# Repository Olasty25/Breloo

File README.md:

# Breloo — a round video keychain

A Ø40 mm keychain that plays actual video. A 1.28" round GC9A01 LCD on the front,
an ESP32-S3 and a microSD slot on the back, a 3.7 V LiPo and USB-C charging.
Drop MP4-derived frames on the card, clip it to your keys, and it loops video in
your pocket.

I am a high-school student from Poland. This is my first 4-layer board and my
first board with a fine-pitch FPC connector.

## What it does

- Plays video and images from a microSD card on a 240×240 round IPS display
- Charges over USB-C, runs from a 400 mAh LiPo
- Backlight is PWM-dimmable from the MCU
- Battery voltage is measured through a divider so the firmware can show charge level
- Fits a 3D-printed case that clips onto a keyring

## Specs

| | |
|---|---|
| Board | Ø40.0 mm circle, 4 layers, 1.6 mm FR-4 |
| MCU | ESP32-S3-WROOM-1-N16R2 (16 MB flash, 2 MB PSRAM) |
| Display | GC9A01 1.28" round IPS 240×240, 12-pin 0.5 mm FPC |
| Storage | microSD (Hirose DM3AT-SF-PEJM5), 1-bit SPI |
| Power | USB-C 5 V → MCP73831 charger → 3.7 V LiPo → AP2112K-3.3 LDO |
| Battery | LP402025, 3.7 V, ~400 mAh |
| Stack-up | F.Cu signals / In1 solid GND / In2 solid +3V3 / B.Cu signals |
| Design rules | 0.2 mm trace / 0.2 mm clearance, 0.6/0.3 mm vias |
| Components | 35 placed parts, 11 top / 24 bottom |
| DRC | 0 errors, 0 unconnected, schematic/PCB parity clean |

## The interesting problem: the display tape is reversed

The GC9A01 flex tape leaves the panel pointing *away* from the board, loops 180°
and comes back into the connector. A 180° fold keeps left and right the same but
flips which face of the tape meets the board, so two things had to change:

1. **The connector has to be dual-contact.** I used XKB `X05A10H12G` (LCSC
   `C528035`), which has contacts on both the top and the bottom of the slot, so
   which way the tape faces stops mattering.
2. **The pad numbering is reversed in the footprint.** In
   `Biblioteka.pretty/FPC_0.5mm_12P_Horizontal_CableReversed.kicad_mod`, pad *N*
   is **display FPC contact N**, not connector pin N. Without this the whole
   12-wire bus lands mirrored and the display never initialises.

The land pattern is taken 1:1 from the JLCEDA/EasyEDA Official Library footprint
`FPC-SMD_X05A10H12G`, so it matches the part the assembler would actually place:
signal pads 0.30 × 0.80 mm on 0.50 mm pitch, hold-downs 0.60 × 1.00 mm at ±3.75 mm.

Footprint geometry source: JLCEDA/EasyEDA Official Library —
https://lceda.cn/ and https://easyeda.com

## Routing notes

Seven display signals have to cross from the left of the FPC connector to targets
on the right, inside a 40 mm circle that is already mostly taken by a 25.5 × 18 mm
radio module. Getting all seven across with 0.2 mm clearance needed the connector
sitting exactly on the board axis — 0.8 mm off and two of them have no legal path.

The inner GND plane is solid except where a battery trace crosses it, and the
plane pair is stitched with vias around the module. One GND pour island above the
connector carries the display's two GND pins and is tied down with a dedicated
stitching via, after nudging a VBAT trace on In1 by 0.4 mm to make room.

## Files

```
images/        board renders, assembly drawings
gerbers/       Breloo-gerbery-JLCPCB-v2.zip — Gerber X2 + Excellon, 12 files
kicad/         full KiCad 10 project: schematic, PCB, custom footprint library
bom/           BOM with LCSC part numbers, and a pick-and-place file
Breloo-schemat.pdf
```

## BOM summary

20 unique parts, ~$8.89 of components per board.

| Part | Designators | LCSC |
|---|---|---|
| ESP32-S3-WROOM-1-N16R2 | U4 | C2913205 |
| microSD socket DM3AT-SF-PEJM5 | J6 | C114218 |
| MCP73831T-2ACI/OT charger | U6 | C424093 |
| USB-C receptacle U262-161N-4BVC11 | J7 | C319148 |
| FPC 0.5 mm 12P dual-contact X05A10H12G | J8 | C528035 |
| B3U-1000P tact switch | SW2 | C231329 |
| AP2112K-3.3 LDO | U5 | C51118 |
| 2N7002 (backlight switch) | Q2 | C8545 |
| red LED 0603 (charge status) | D2 | C2286 |
| 0603 / 0805 passives | 24 parts | see `bom/Breloo_BOM.csv` |

Full list with quantities: [`bom/Breloo_BOM.csv`](bom/Breloo_BOM.csv)

## Manufacturing

JLCPCB, 4 layers, 40 × 40 mm, 1.6 mm, lead-free HASL, **minimum via hole 0.2 mm**
(there are 12 thermal vias under the module and 2 next to the FPC connector).
I am assembling the boards by hand with hot air and an iron.

## Assembly drawings

Blue dot = pin 1 (cathode on D2). Dotted outlines are not populated:
TP2–TP6 are test points and J9 is the battery solder pad pair.

## Status

- [x] Schematic
- [x] Layout, 4 layers, DRC clean
- [x] Footprint verified against the manufacturer's land pattern
- [x] Gerbers exported and checked (outline exactly 40.000 mm, 60 plated holes)
- [ ] Boards ordered
- [ ] Hand assembly
- [ ] Firmware

## License

MIT for the design files. See [LICENSE](LICENSE).

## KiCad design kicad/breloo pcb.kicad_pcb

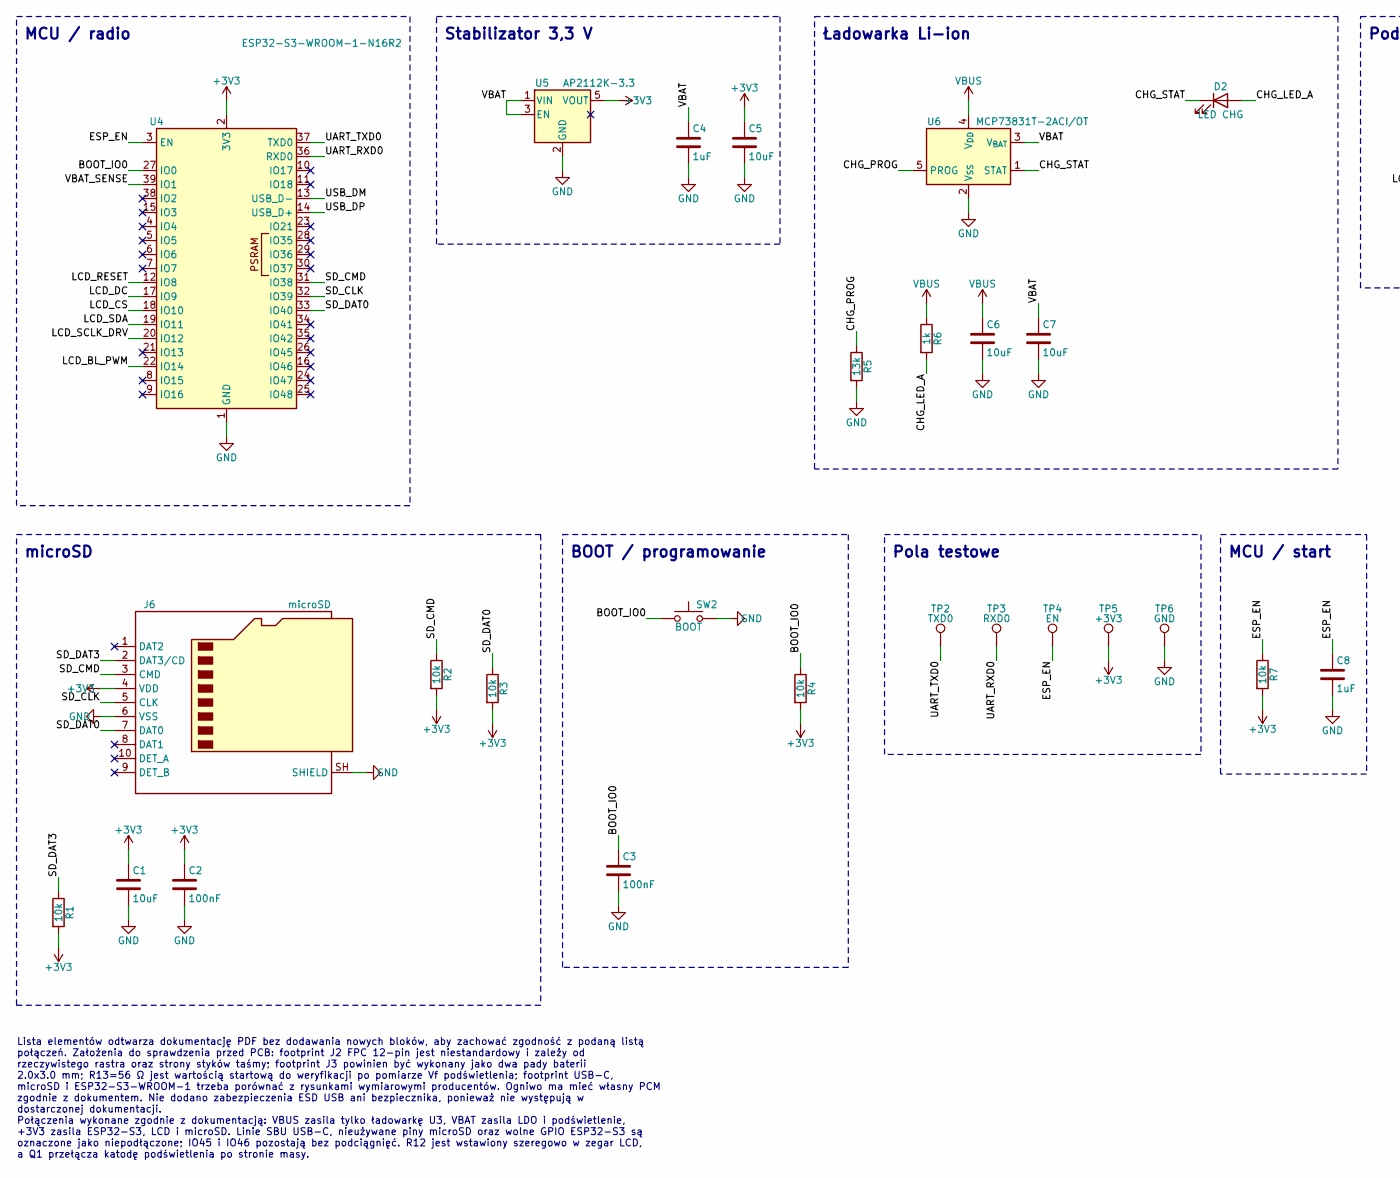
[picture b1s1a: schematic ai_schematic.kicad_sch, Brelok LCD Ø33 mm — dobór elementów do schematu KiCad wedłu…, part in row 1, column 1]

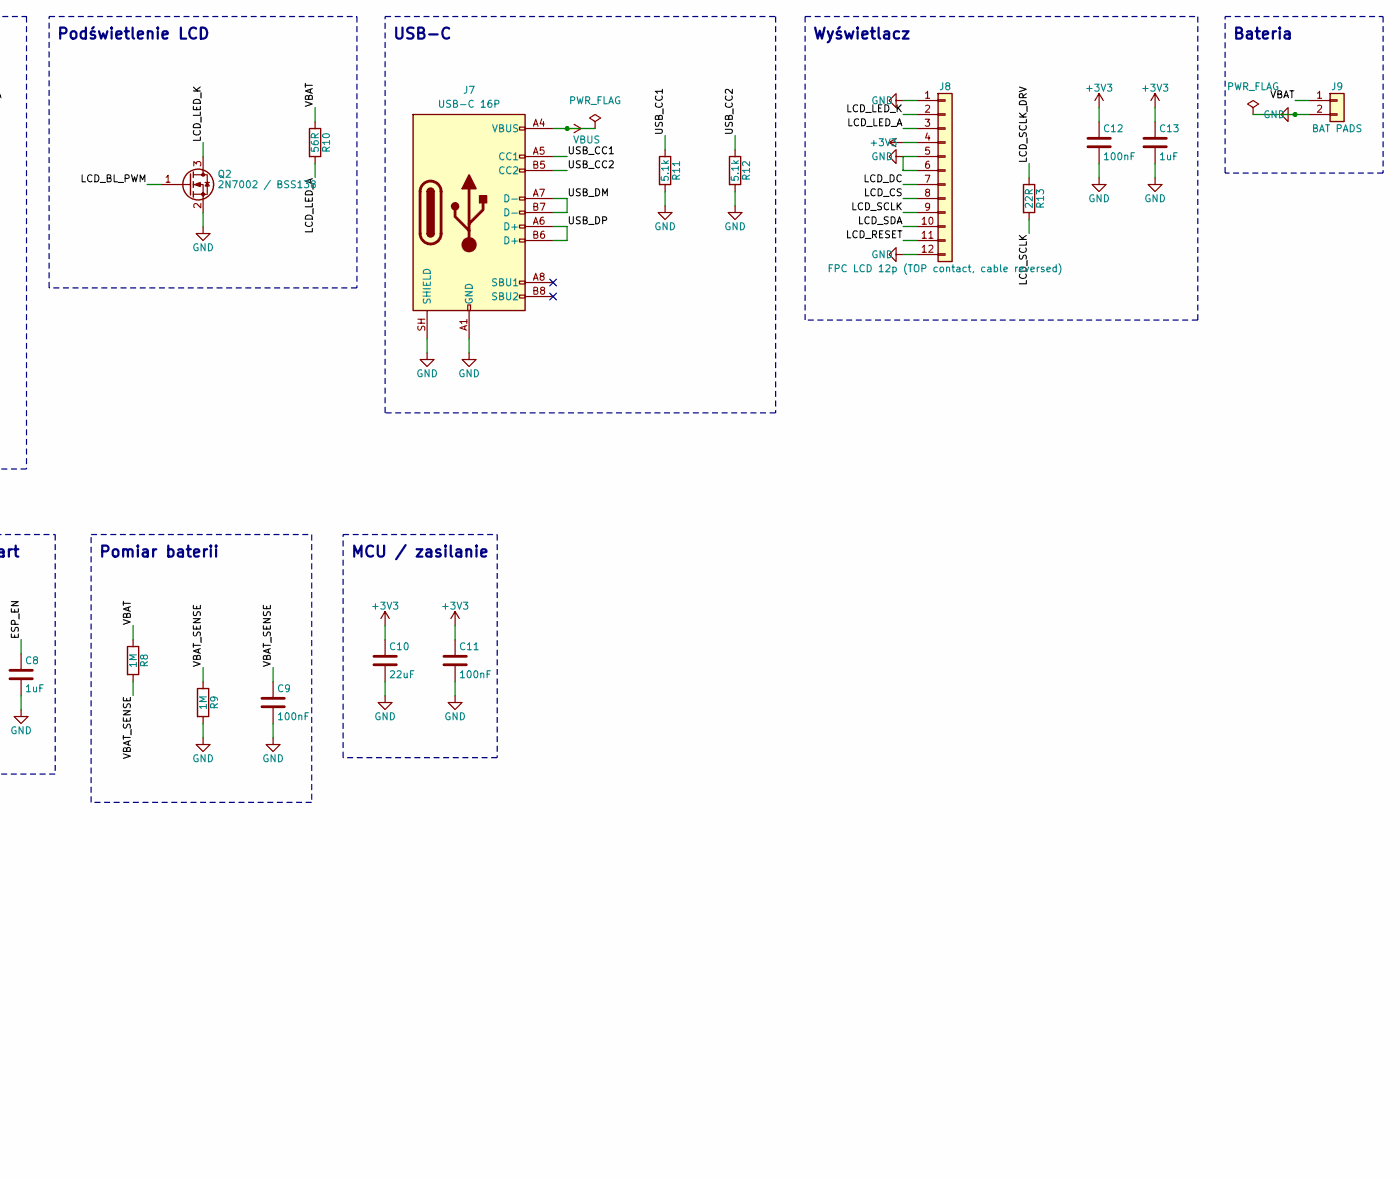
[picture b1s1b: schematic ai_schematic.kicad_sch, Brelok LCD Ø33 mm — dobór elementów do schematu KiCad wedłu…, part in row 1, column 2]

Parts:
C1, C5, C6, C7: 10uF; C_0805_2012Metric
C2, C3, C9, C11, C12: 100nF; C_0603_1608Metric
C4, C8, C13: 1uF; C_0603_1608Metric
C10: 22uF; C_0805_2012Metric
D2: LED CHG; LED_0603_1608Metric
J6: microSD; microSD_HC_Hirose_DM3AT-SF-PEJM5
J7: USB-C 16P; USB_C_Receptacle_XKB_U262-16XN-4BVC11
J8: FPC LCD 12p (TOP contact, cable reversed); FPC_0.5mm_12P_Horizontal_CableReversed
J9: BAT PADS; BAT_Pads_LP402025
Q2: 2N7002 / BSS138; SOT-23
R1, R2, R3, R4, R7: 10k; R_0603_1608Metric
R5: 13k; R_0603_1608Metric
R6: 1k; R_0603_1608Metric
R8, R9: 1M; R_0603_1608Metric
R10: 56R; R_0603_1608Metric
R11, R12: 5.1k; R_0603_1608Metric
R13: 22R; R_0603_1608Metric
SW2: BOOT; SW_SPST_B3U-1000P
TP2: TXD0; TestPoint_Pad_1.0x1.0mm
TP3: RXD0; TestPoint_Pad_1.0x1.0mm
TP4: EN; TestPoint_Pad_1.0x1.0mm
TP5: +3V3; TestPoint_Pad_1.0x1.0mm
TP6: GND; TestPoint_Pad_1.0x1.0mm
U4: ESP32-S3-WROOM-1-N16R2; ESP32-S3-WROOM-1
U5: AP2112K-3.3; SOT-23-5
U6: MCP73831T-2ACI/OT; SOT-23-5

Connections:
+3V3: C1.1, C2.1, C5.1, C10.1, C11.1, C12.1, C13.1, J6.4 (VDD), J8.4, R1.2, R2.2, R3.2, R4.2, R7.2, TP5.1 (1_1), U4.2 (3V3), U5.5 (VOUT)
/Schematic AI Breloo/BOOT_IO0: C3.1, R4.1, SW2.1, U4.27 (IO0)
/Schematic AI Breloo/CHG_LED_A: D2.2 (A), R6.2
/Schematic AI Breloo/CHG_PROG: R5.1, U6.5 (PROG)
/Schematic AI Breloo/CHG_STAT: D2.1 (K), U6.1 (STAT)
/Schematic AI Breloo/ESP_EN: C8.1, R7.1, TP4.1 (1_1), U4.3 (EN)
/Schematic AI Breloo/LCD_BL_PWM: Q2.1 (G), U4.22 (IO14)
/Schematic AI Breloo/LCD_CS: J8.8, U4.18 (IO10)
/Schematic AI Breloo/LCD_DC: J8.7, U4.17 (IO9)
/Schematic AI Breloo/LCD_LED_A: J8.3, R10.2
/Schematic AI Breloo/LCD_LED_K: J8.2, Q2.3 (D)
/Schematic AI Breloo/LCD_RESET: J8.11, U4.12 (IO8)
/Schematic AI Breloo/LCD_SCLK: J8.9, R13.2
/Schematic AI Breloo/LCD_SCLK_DRV: R13.1, U4.20 (IO12)
/Schematic AI Breloo/LCD_SDA: J8.10, U4.19 (IO11)
/Schematic AI Breloo/SD_CLK: J6.5 (CLK), U4.32 (IO39)
/Schematic AI Breloo/SD_CMD: J6.3 (CMD), R2.1, U4.31 (IO38)
/Schematic AI Breloo/SD_DAT0: J6.7 (DAT0), R3.1, U4.33 (IO40)
/Schematic AI Breloo/SD_DAT3: J6.2 (DAT3/CD), R1.1
/Schematic AI Breloo/UART_RXD0: TP3.1 (1_1), U4.36 (RXD0)
/Schematic AI Breloo/UART_TXD0: TP2.1 (1_1), U4.37 (TXD0)
/Schematic AI Breloo/USB_CC1: J7.A5 (CC1), R11.1
/Schematic AI Breloo/USB_CC2: J7.B5 (CC2), R12.1
/Schematic AI Breloo/USB_DM: J7.A7 (D-), J7.B7 (D-), U4.13 (USB_D-)
/Schematic AI Breloo/USB_DP: J7.A6 (D+), J7.B6 (D+), U4.14 (USB_D+)
/Schematic AI Breloo/VBAT: C4.1, C7.1, J9.1, R8.1, R10.1, U5.1 (VIN), U5.3 (EN), U6.3 (V_{BAT})
/Schematic AI Breloo/VBAT_SENSE: C9.1, R8.2, R9.1, U4.39 (IO1)
GND: C1.2, C2.2, C3.2, C4.2, C5.2, C6.2, C7.2, C8.2, C9.2, C10.2, C11.2, C12.2, C13.2, J6.6 (VSS), J6.SH (SHIELD), J7.A1 (GND), J7.A12 (GND), J7.B1 (GND), J7.B12 (GND), J7.SH (SHIELD), J8.1, J8.5, J8.6, J8.12, J9.2, Q2.2 (S), R5.2, R9.2, R11.2, R12.2, SW2.2, TP6.1 (1_1), U4.1 (GND), U4.40 (GND), U4.41 (GND), U5.2 (GND), U6.2 (V_{SS})
VBUS: C6.1, J7.A4 (VBUS), J7.A9 (VBUS), J7.B4 (VBUS), J7.B9 (VBUS), R6.1, U6.4 (V_{DD})

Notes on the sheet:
Wyświetlacz
MCU / start
USB-C
Bateria
Ładowarka Li-ion
Pomiar baterii
MCU / radio
Podświetlenie LCD
BOOT / programowanie
Stabilizator 3,3 V
microSD
Lista elementów odtwarza dokumentację PDF bez dodawania nowych bloków, aby zachować zgodność z podaną listą połączeń. Założenia do sprawdzenia przed PCB: footprint J2 FPC 12-pin jest niestandardowy i zależy od rzeczywistego rastra oraz strony styków taśmy; footprint J3 powinien być wykonany jako dw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
MCU / zasilanie
Pola testowe

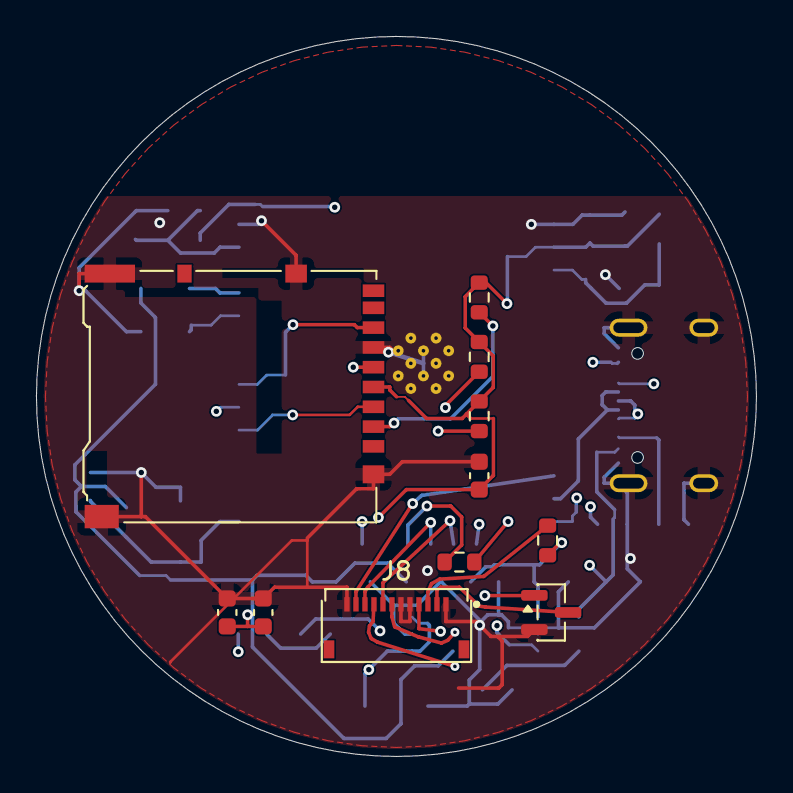
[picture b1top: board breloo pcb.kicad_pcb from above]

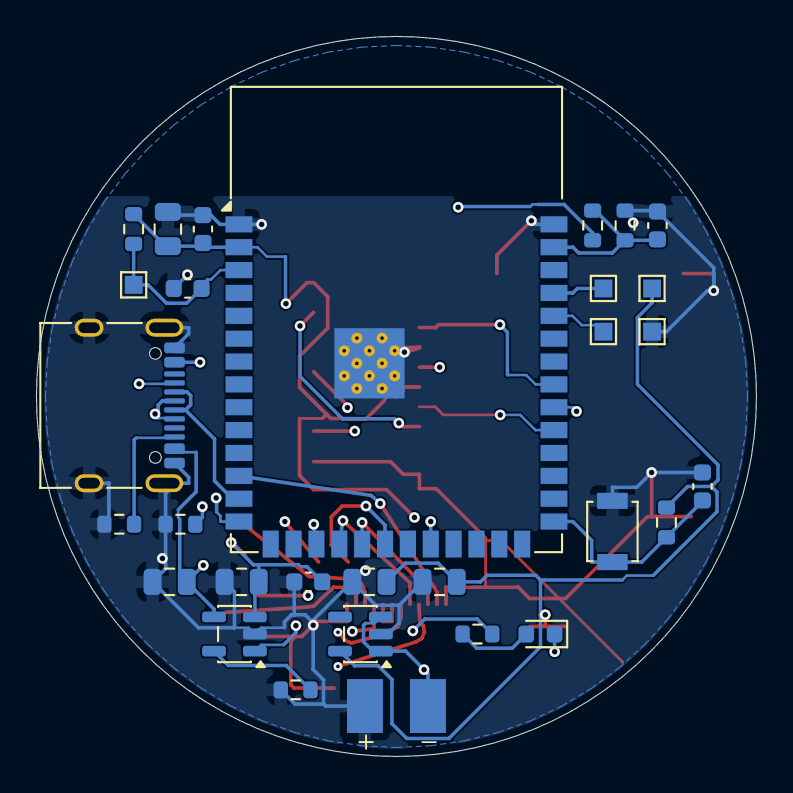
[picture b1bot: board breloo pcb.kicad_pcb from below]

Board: 4 copper layers, 40.0 x 40.0 mm, 41 parts (30 on the bottom side), 29 nets.

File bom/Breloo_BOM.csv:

Comment,Designator,Footprint,LCSC Part #,Quantity
10uF 25V X5R 0805,"C1,C5,C6,C7",C_0805_2012Metric,C15850,4
100nF 50V X7R 0603,"C2,C3,C9,C11,C12",C_0603_1608Metric,C14663,5
1uF 50V X5R 0603,"C4,C8,C13",C_0603_1608Metric,C15849,3
22uF 25V X5R 0805,C10,C_0805_2012Metric,C45783,1
LED Red 0603,D2,LED_0603_1608Metric,C2286,1
microSD DM3AT-SF-PEJM5,J6,microSD_HC_Hirose_DM3AT-SF-PEJM5,C114218,1
USB-C U262-161N-4BVC11,J7,USB_C_Receptacle_XKB_U262-16XN-4BVC11,C319148,1
FPC 0.5mm 12P X05A10H12G,J8,FPC_0.5mm_12P_Horizontal_CableReversed,C528035,1
2N7002 SOT-23,Q2,SOT-23,C8545,1
10k 1% 0603,"R1,R2,R3,R4,R7",R_0603_1608Metric,C25804,5
13k 1% 0603,R5,R_0603_1608Metric,C22797,1
1k 1% 0603,R6,R_0603_1608Metric,C21190,1
1M 1% 0603,"R8,R9",R_0603_1608Metric,C22935,2
56R 1% 0603,R10,R_0603_1608Metric,C25196,1
5.1k 1% 0603,"R11,R12",R_0603_1608Metric,C23186,2
22R 1% 0603,R13,R_0603_1608Metric,C23345,1
B3U-1000P,SW2,SW_SPST_B3U-1000P,C231329,1
ESP32-S3-WROOM-1-N16R2,U4,ESP32-S3-WROOM-1,C2913205,1
AP2112K-3.3TRG1 SOT-23-5,U5,SOT-23-5,C51118,1
MCP73831T-2ACI/OT SOT-23-5,U6,SOT-23-5,C424093,1
